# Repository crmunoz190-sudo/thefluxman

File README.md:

# thefluxman
This is the schematic and PCB to my guitar pedal, the flux man.
12K and 100Ohm resistors used instead of specific values to save on JLCPCB extended part fees.

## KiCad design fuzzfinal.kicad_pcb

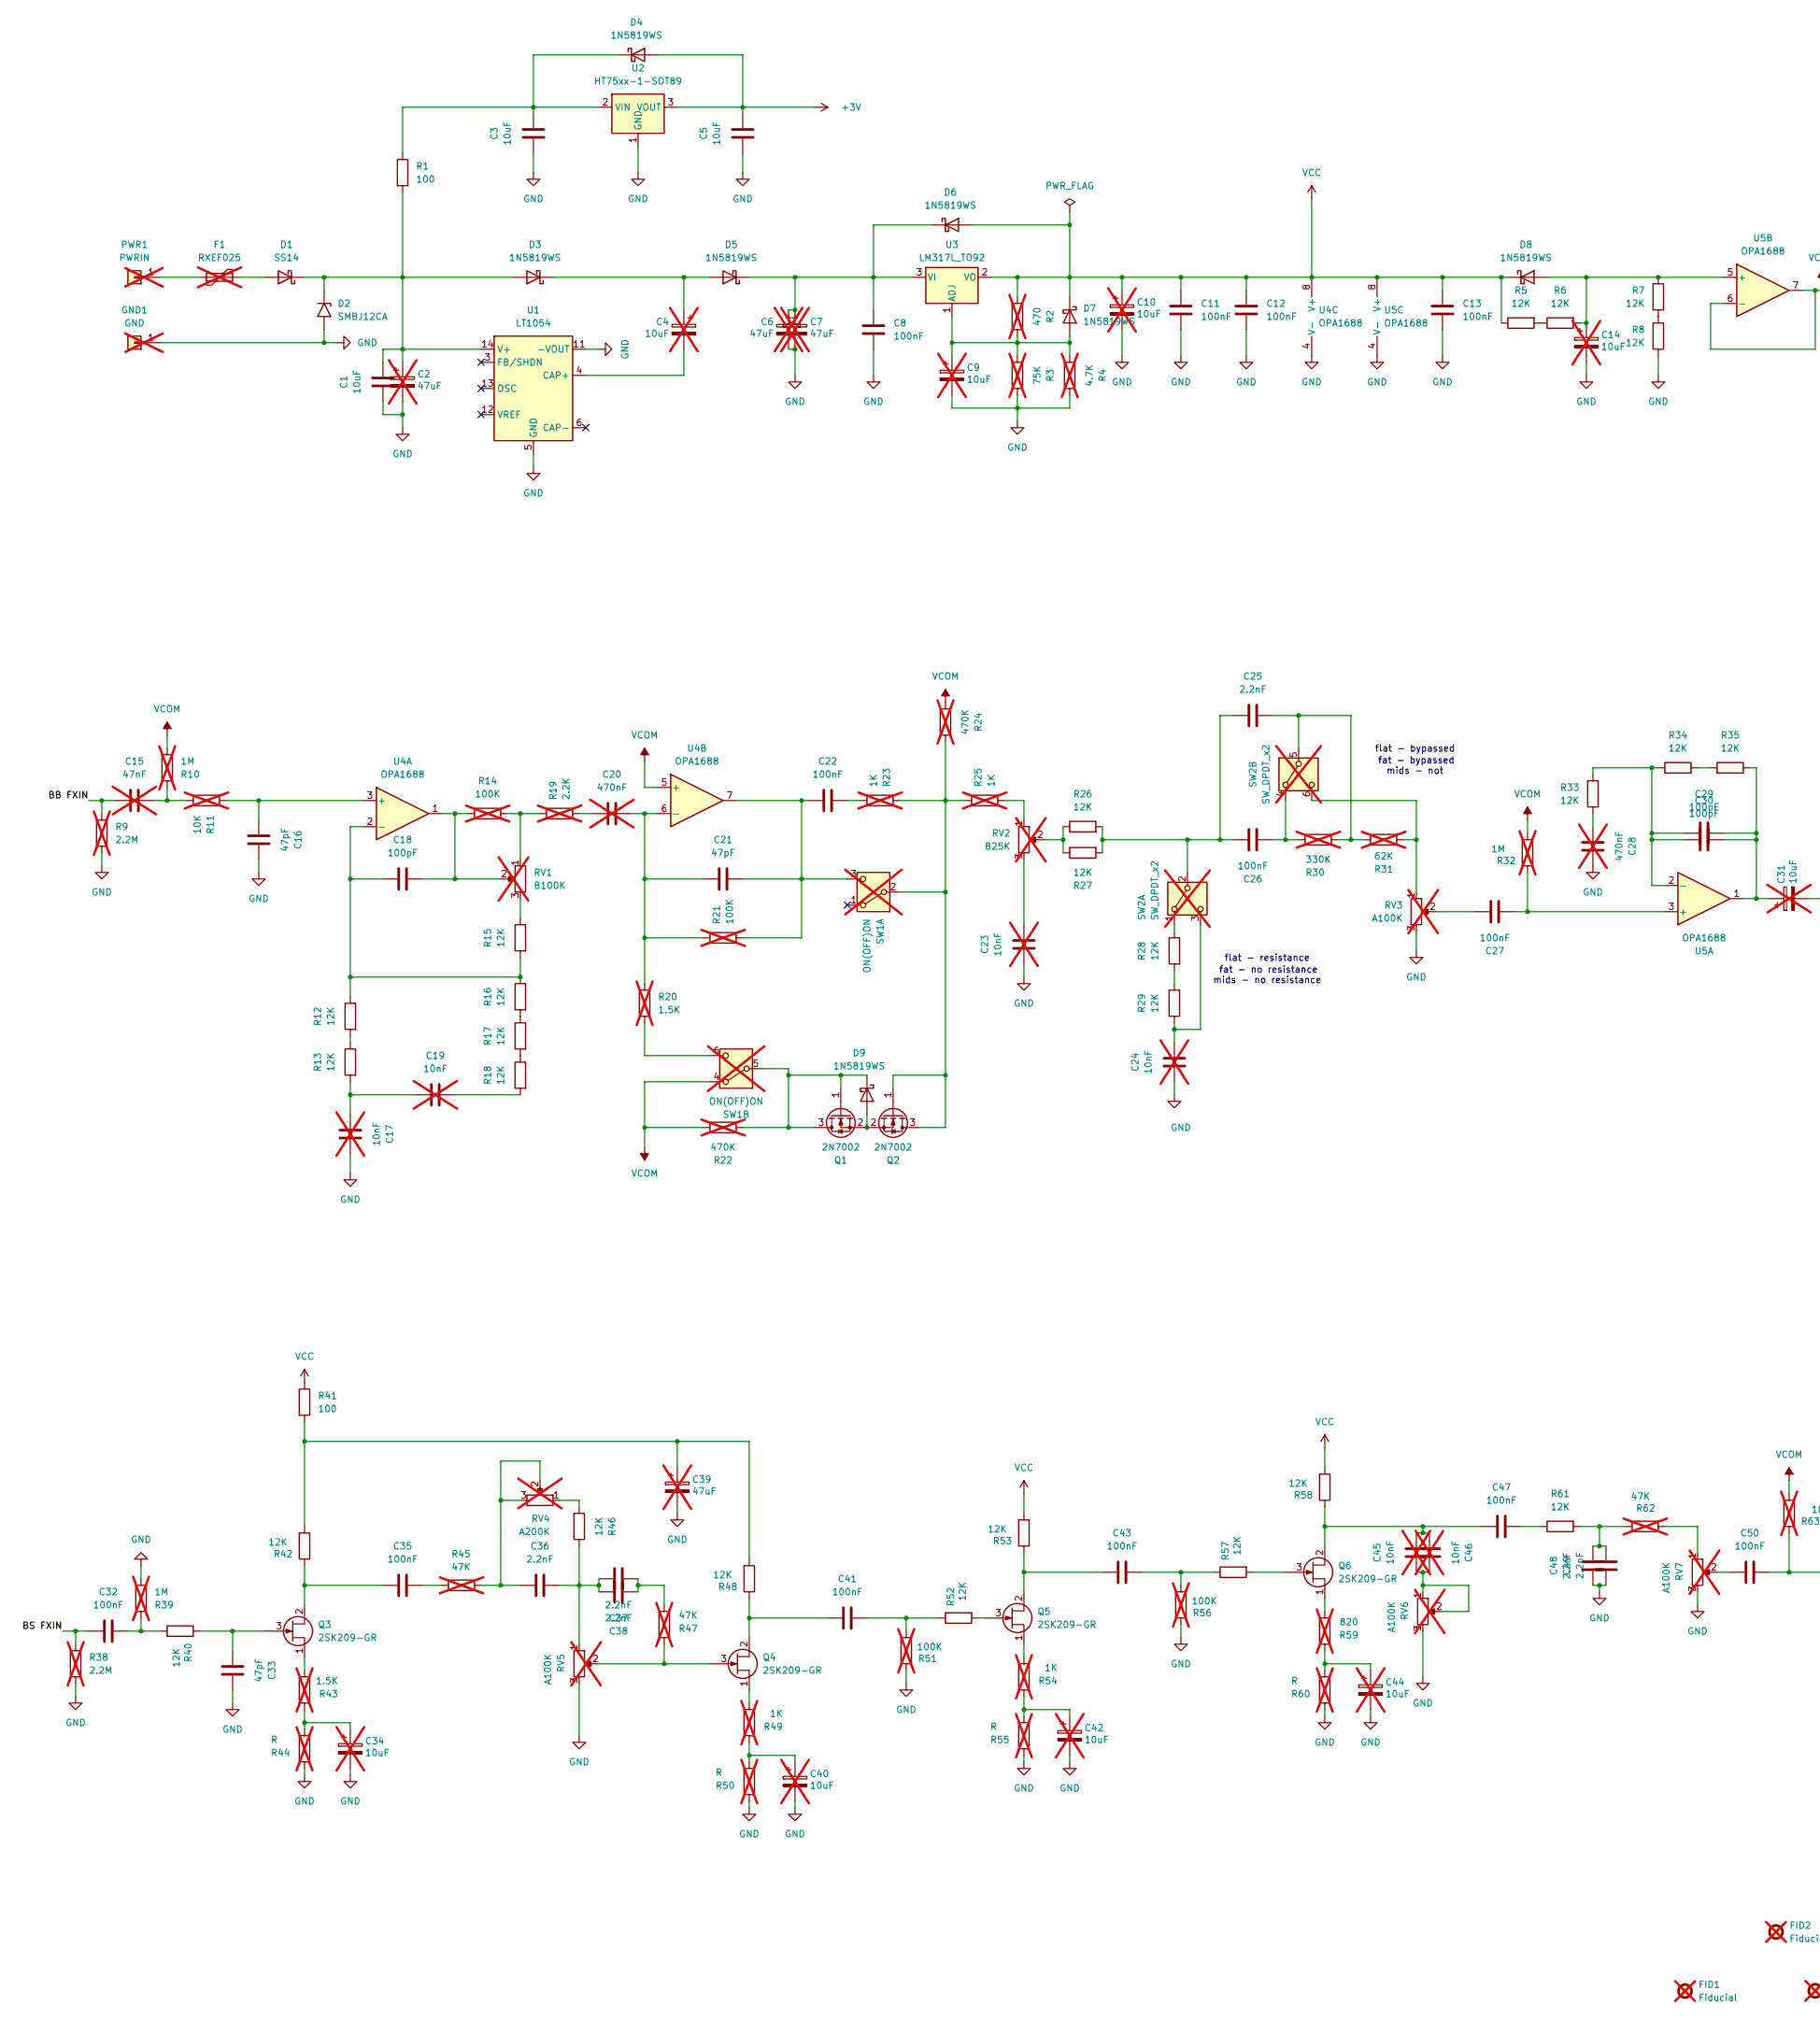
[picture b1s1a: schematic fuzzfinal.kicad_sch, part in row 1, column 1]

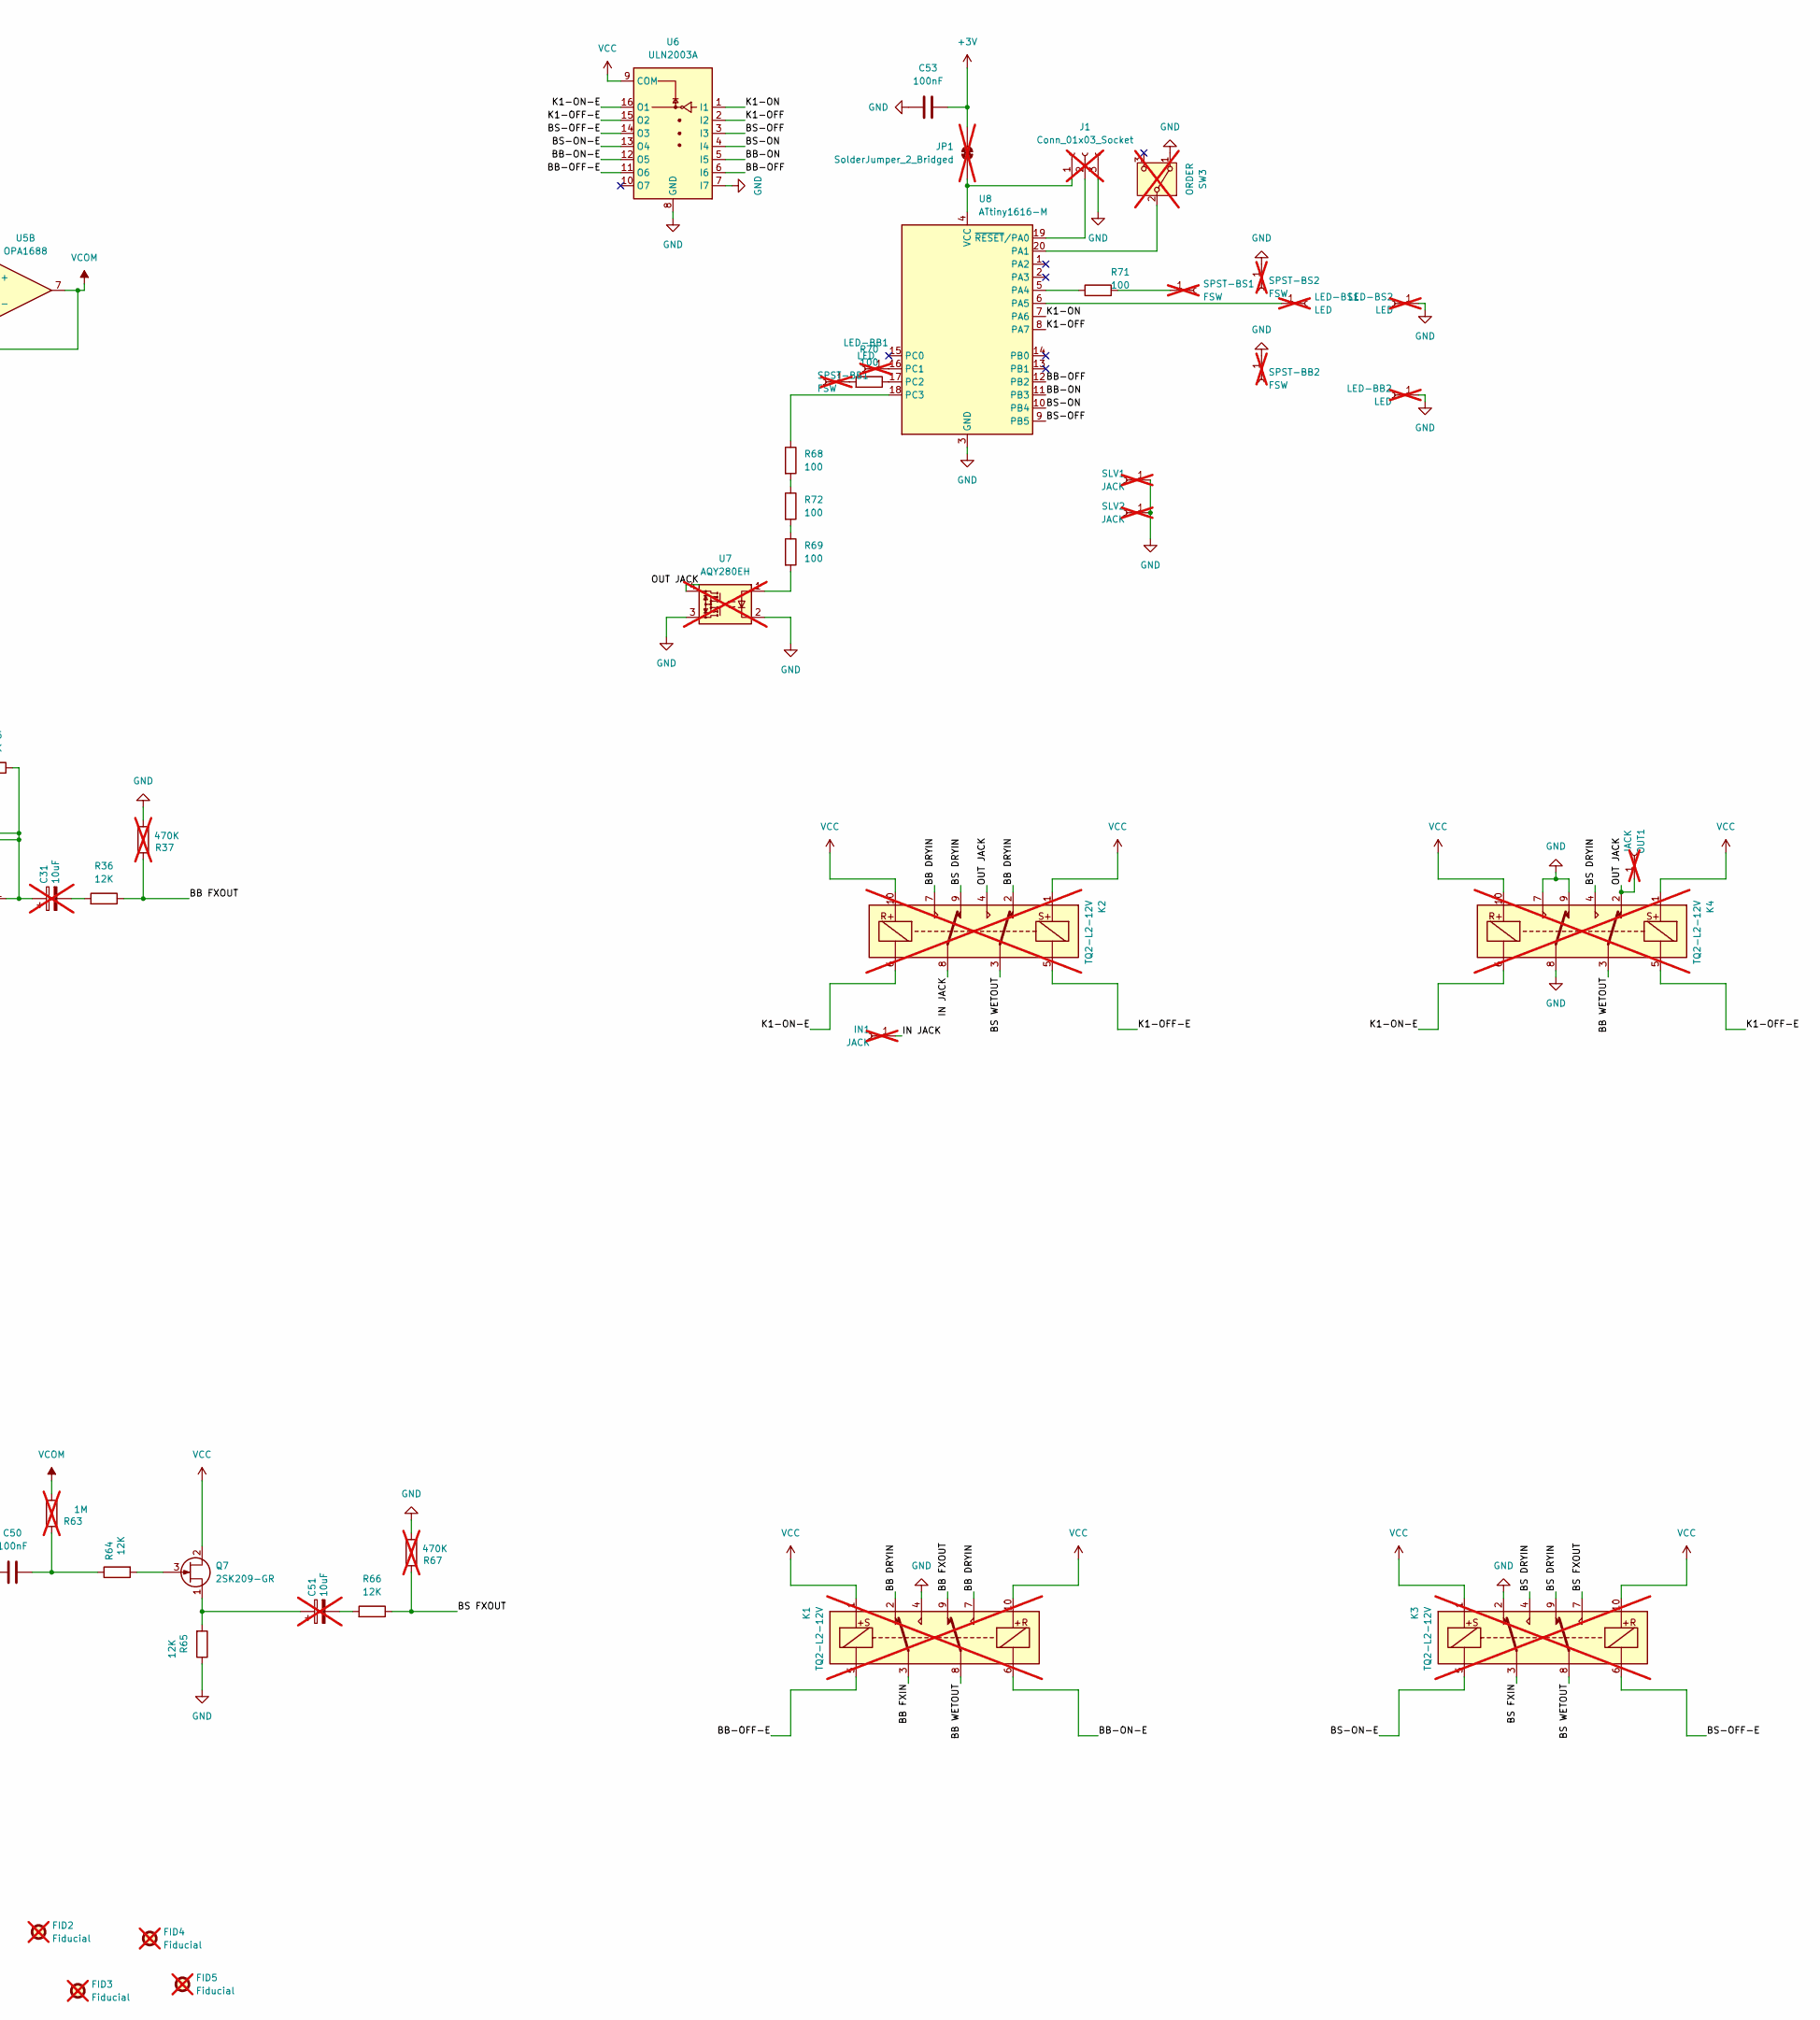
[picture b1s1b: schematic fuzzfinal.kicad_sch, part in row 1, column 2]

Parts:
C1, C3, C5: 10uF; C_0603_1608Metric; LCSC C96446
C2, C6, C7, C39: 47uF; CP_Radial_D5.0mm_P2.00mm; not fitted
C4, C9, C10, C14, C31, C34, C40, C42, C44, C51: 10uF; CP_Radial_D5.0mm_P2.00mm; not fitted
C8, C11, C12, C13, C22, C26, C27, C32, C35, C41, C43, C47, C50, C53: 100nF; C_1206_3216Metric; LCSC C363929
C15: 47nF; C_Rect_L7.2mm_W2.5mm_P5.00mm_FKS2_FKP2_MKS2_MKP2; not fitted
C16, C21, C33: 47pF; C_0402_1005Metric; LCSC C1567
C17, C19, C23, C24, C45, C46: 10nF; C_Rect_L7.2mm_W2.5mm_P5.00mm_FKS2_FKP2_MKS2_MKP2; not fitted
C18, C29, C30: 100pF; C_0402_1005Metric; LCSC C1546
C20, C28: 470nF; C_Rect_L7.2mm_W3.5mm_P5.00mm_FKS2_FKP2_MKS2_MKP2; not fitted
C25, C36, C37, C38, C48, C49: 2.2nF; C_0805_2012Metric; LCSC C28260
D1: SS14; D_SMA; LCSC C2480
D2: SMBJ12CA; D_SMB; LCSC C19077566
D3, D4, D5, D6, D7, D8, D9: 1N5819WS; D_SOD-323; LCSC C191023
F1: RXEF025; C_Rect_L7.2mm_W3.0mm_P5.00mm_FKS2_FKP2_MKS2_MKP2; not fitted
FID1, FID2, FID3, FID4, FID5: Fiducial; Fiducial_1mm_Mask2mm; not fitted
GND1: GND; Solder Wire, DC Jack NO RELIEF; not fitted
IN1: JACK; Solder Wire, DC Jack NO RELIEF; not fitted
J1: Conn_01x03_Socket; PinSocket_1x03_P2.54mm_Vertical; not fitted
JP1: SolderJumper_2_Bridged; SolderJumper-2_P1.3mm_Open_TrianglePad1.0x1.5mm; not fitted
K1, K2, K3, K4: TQ2-L2-12V; not fitted
LED-BB1, LED-BB2: LED; Solder Wire, DC Jack NO RELIEF; not fitted
LED-BS1, LED-BS2: LED; Solder Wire, DC Jack NO RELIEF; not fitted
OUT1: JACK; Solder Wire, DC Jack NO RELIEF; not fitted
PWR1: PWRIN; Solder Wire, DC Jack NO RELIEF; not fitted
Q1, Q2: 2N7002; SOT-323_SC-70; LCSC C7420322
Q3, Q4, Q5, Q6, Q7: 2SK209-GR; SC-59; LCSC C61792
R1, R41, R68, R69, R70, R71, R72: 100; R_0603_1608Metric; LCSC C22775
R2: 470; R_Axial_DIN0207_L6.3mm_D2.5mm_P7.62mm_Horizontal; not fitted
R3: 75K; R_Axial_DIN0204_L3.6mm_D1.6mm_P5.08mm_Horizontal; not fitted
R4: 4.7K; R_Axial_DIN0204_L3.6mm_D1.6mm_P7.62mm_Horizontal; not fitted
R5, R6, R7, R8, R12, R13, R15, R16, R17, R18, R26, R27, R28, R29, R33, R34, R35, R36, R40, R42, R46, R48, R52, R53, R57, R58, R61, R64, R65, R66: 12K; R_0402_1005Metric; LCSC C784579
R9, R38: 2.2M; R_Axial_DIN0204_L3.6mm_D1.6mm_P5.08mm_Horizontal; not fitted
R10, R32, R39, R63: 1M; R_Axial_DIN0204_L3.6mm_D1.6mm_P5.08mm_Horizontal; not fitted
R11: 10K; R_Axial_DIN0207_L6.3mm_D2.5mm_P7.62mm_Horizontal; not fitted
R14, R21, R51, R56: 100K; R_Axial_DIN0204_L3.6mm_D1.6mm_P5.08mm_Horizontal; not fitted
R19: 2.2K; R_Axial_DIN0207_L6.3mm_D2.5mm_P7.62mm_Horizontal; not fitted
R20: 1.5K; R_Axial_DIN0207_L6.3mm_D2.5mm_P5.08mm_Vertical; not fitted
R22, R24, R37, R67: 470K; R_Axial_DIN0204_L3.6mm_D1.6mm_P5.08mm_Horizontal; not fitted
R23, R25, R49, R54: 1K; R_Axial_DIN0207_L6.3mm_D2.5mm_P7.62mm_Horizontal; not fitted
R30: 330K; R_Axial_DIN0204_L3.6mm_D1.6mm_P5.08mm_Horizontal; not fitted
R31: 62K; R_Axial_DIN0204_L3.6mm_D1.6mm_P5.08mm_Horizontal; not fitted
R43: 1.5K; R_Axial_DIN0207_L6.3mm_D2.5mm_P7.62mm_Horizontal; not fitted
R44, R50, R55, R60: R; R_Axial_DIN0207_L6.3mm_D2.5mm_P7.62mm_Horizontal; not fitted
R45, R47, R62: 47K; R_Axial_DIN0204_L3.6mm_D1.6mm_P5.08mm_Horizontal; not fitted
R59: 820; R_Axial_DIN0207_L6.3mm_D2.5mm_P7.62mm_Horizontal; not fitted
RV1: B100K; SingleTaper16mmAlpha; not fitted
RV2: B25K; SingleTaper16mmAlpha; not fitted
RV3, RV5, RV6, RV7: A100K; SingleTaper16mmAlpha; not fitted
RV4: A200K; SingleTaper16mmAlpha; not fitted
SLV1, SLV2: JACK; Solder Wire, DC Jack NO RELIEF; not fitted
SPST-BB1, SPST-BB2: FSW; Solder Wire, DC Jack NO RELIEF; not fitted
SPST-BS1, SPST-BS2: FSW; Solder Wire, DC Jack NO RELIEF; not fitted
SW1: ON(OFF)ON; 2pdt; not fitted
SW2: SW_DPDT_x2; 2pdt; not fitted
SW3: ORDER; spdt; not fitted
U1: LT1054; SOIC-16W_7.5x10.3mm_P1.27mm; LCSC C2071368
U2: HT75xx-1-SOT89; SOT-89-3; LCSC C14289
U3: LM317L_TO92; SOT-89-3; LCSC C112537
U4, U5: OPA1688; SOIC-8_3.9x4.9mm_P1.27mm; LCSC C206212
U6: ULN2003A; SOIC-16_3.9x9.9mm_P1.27mm; LCSC C7512
U7: AQY280EH; DIP-4_W10.16mm; not fitted
U8: ATtiny1616-M; QFN-20-1EP_3x3mm_P0.4mm_EP1.65x1.65mm; LCSC C507118

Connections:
+3V: C5.1, C53.2, D4.2 (A), JP1.2 (B), U2.3 (VOUT)
/BB DRYIN: K1.2, K1.7, K2.2, K2.7
/BB FXIN: C15.1, K1.3, R9.1
/BB FXOUT: K1.9, R36.1, R37.1
/BB WETOUT: K1.8, K4.3
/BB-OFF: U6.6 (I6), U8.12 (PB2)
/BB-OFF-E: K1.5, U6.11 (O6)
/BB-ON: U6.5 (I5), U8.11 (PB3)
/BB-ON-E: K1.6, U6.12 (O5)
/BS DRYIN: K2.9, K3.4, K3.9, K4.4
/BS FXIN: C32.1, K3.3, R38.1
/BS FXOUT: K3.7, R66.1, R67.1
/BS WETOUT: K2.3, K3.8
/BS-OFF: U6.3 (I3), U8.9 (PB5)
/BS-OFF-E: K3.6, U6.14 (O3)
/BS-ON: U6.4 (I4), U8.10 (PB4)
/BS-ON-E: K3.5, U6.13 (O4)
/IN JACK: IN1.1 (Pin_1_1), K2.8
/K1-OFF: U6.2 (I2), U8.8 (PA7)
/K1-OFF-E: K2.5, K4.5, U6.15 (O2)
/K1-ON: U6.1 (I1), U8.7 (PA6)
/K1-ON-E: K2.6, K4.6, U6.16 (O1)
/OUT JACK: K2.4, K4.2, OUT1.1 (Pin_1_1), U7.4
GND: C1.2, C2.2, C3.2, C5.2, C6.2, C7.2, C8.1, C9.2, C10.2, C11.1, C12.1, C13.1, C14.2, C16.1, C17.1, C23.2, C24.2, C28.2, C33.1, C34.2, C39.2, C40.2, C42.2, C44.2, C48.2, C49.2, C53.1, D2.2 (A2), GND1.1 (Pin_1_1), J1.3, K1.4, K3.2, K4.7, K4.8, K4.9, LED-BB2.1 (Pin_1_1), LED-BS2.1 (Pin_1_1), R3.1, R4.1, R8.1, R9.2, R37.2, R38.2, R39.2, R44.1, R50.1, R51.1, R55.1, R56.1, R60.1, R65.1, R67.2, RV3.3, RV5.3, RV6.3, RV7.3, SLV1.1 (Pin_1_1), SLV2.1 (Pin_1_1), SPST-BB2.1 (Pin_1_1), SPST-BS2.1 (Pin_1_1), SW3.1 (A), U1.5 (GND), U1.11 (-VOUT), U2.1 (GND), U4.4 (V-), U5.4 (V-), U6.7 (I7), U6.8 (GND), U7.2, U7.3, U8.3 (GND), U8.21 (GND)
unnamed: C15.2, R10.1, R11.2
unnamed: C17.2, C19.2, R13.2
unnamed: C18.1, R14.2, RV1.2, U4.1
unnamed: C19.1, R18.2
unnamed: C20.1, R19.2
unnamed: C22.1, R23.2
unnamed: C23.1, RV2.3
unnamed: C27.1, RV3.2
unnamed: C28.1, R33.1
unnamed: C29.1, C30.2, C31.1, R35.1, U5.1
unnamed: C31.2, R36.2
unnamed: C32.2, R39.1, R40.2
unnamed: C34.1, R43.1, R44.2
unnamed: C35.2, R45.2
unnamed: C36.1, R45.1, RV4.2, RV4.3
unnamed: C36.2, C37.1, C38.1, R46.1, RV5.1
unnamed: C37.2, C38.2, R47.2
unnamed: C39.1, R41.2, R42.2, R48.2
unnamed: C40.1, R49.1, R50.2
unnamed: C41.2, R51.2, R52.1
unnamed: C42.1, R54.1, R55.2
unnamed: C43.2, R56.2, R57.1
unnamed: C44.1, R59.1, R60.2
unnamed: C45.2, C46.2, RV6.1, RV6.2
unnamed: C47.1, R61.1
unnamed: C48.1, C49.1, R61.2, R62.1
unnamed: C50.1, R63.1, R64.1
unnamed: C50.2, RV7.2
unnamed: C51.2, R66.2
unnamed: D1.2 (A), F1.2
unnamed: C1.1, C2.1, D1.1 (K), D2.1 (A1), D3.2 (A), R1.2, U1.14 (V+)
unnamed: C4.1, D3.1 (K), D5.2 (A)
unnamed: C3.1, D4.1 (K), R1.1, U2.2 (VIN)
unnamed: C6.1, C7.1, C8.2, D5.1 (K), D6.1 (K), U3.3 (VI)
unnamed: C9.1, D7.2 (A), R2.1, R3.2, R4.2, U3.1 (ADJ)
unnamed: C14.1, D8.2 (A), R6.2, R7.2, U5.5 (+)
unnamed: D9.2 (A), Q1.2 (S), Q2.2 (S)
unnamed: D9.1 (K), Q1.1 (G), Q1.3 (D), R22.1, SW1.5 (B)
unnamed: J1.1, JP1.1 (A), U8.4 (VCC)
unnamed: J1.2, U8.19 (~RESET/PA0)
unnamed: LED-BB1.1 (Pin_1_1), U8.16 (PC1)
unnamed: LED-BS1.1 (Pin_1_1), U8.6 (PA5)
unnamed: F1.1, PWR1.1 (Pin_1_1)
unnamed: Q2.1 (G), Q2.3 (D), R23.1, R24.2, R25.1, SW1.2 (B)
unnamed: C35.1, Q3.2 (D), R42.1
unnamed: C33.2, Q3.3 (G), R40.1
unnamed: Q3.1 (S), R43.2
unnamed: C41.1, Q4.2 (D), R48.1
unnamed: Q4.3 (G), R47.1, RV5.2
unnamed: Q4.1 (S), R49.2
unnamed: C43.1, Q5.2 (D), R53.1
unnamed: Q5.3 (G), R52.2
unnamed: Q5.1 (S), R54.2
unnamed: C45.1, C46.1, C47.2, Q6.2 (D), R58.1
unnamed: Q6.3 (G), R57.2
unnamed: Q6.1 (S), R59.2
unnamed: Q7.3 (G), R64.2
unnamed: C51.1, Q7.1 (S), R65.2
unnamed: R5.2, R6.1
unnamed: R7.1, R8.2
unnamed: R12.2, R13.1
unnamed: R14.1, R19.1, RV1.1
unnamed: R15.1, RV1.3
unnamed: R16.2, R17.1
unnamed: R17.2, R18.1
unnamed: R25.2, RV2.1
unnamed: R26.1, R27.1, RV2.2
unnamed: R28.2, R29.2
unnamed: R34.2, R35.2
unnamed: R46.2, RV4.1
unnamed: R62.2, RV7.1
unnamed: R68.2, R72.1
unnamed: R69.1, R72.2
unnamed: R69.2, U7.1
unnamed: R70.2, SPST-BB1.1 (Pin_1_1)
unnamed: R71.2, SPST-BS1.1 (Pin_1_1)
unnamed: C21.1, C22.2, R21.2, SW1.3 (C), U4.7
unnamed: R20.2, SW1.6 (C)
unnamed: R28.1, SW2.1 (A)
unnamed: C25.1, C26.1, R26.2, R27.2, SW2.2 (B)
unnamed: C24.1, R29.1, SW2.3 (C)
unnamed: C26.2, R30.1, SW2.4 (A)
unnamed: C25.2, R30.2, R31.1, SW2.5 (B)
unnamed: R31.2, RV3.1, SW2.6 (C)
unnamed: SW3.2 (B), U8.20 (PA1)
unnamed: C4.2, U1.4 (CAP+)
unnamed: C16.2, R11.1, U4.3 (+)
unnamed: C18.2, R12.1, R15.2, R16.1, U4.2 (-)
unnamed: C20.2, C21.2, R20.1, R21.1, U4.6 (-)
unnamed: C27.2, R32.1, U5.3 (+)
unnamed: C29.2, C30.1, R33.2, R34.1, U5.2 (-)
unnamed: R71.1, U8.5 (PA4)
unnamed: R70.1, U8.17 (PC2)
unnamed: R68.1, U8.18 (PC3)
VCC: C10.1, C11.2, C12.2, C13.2, D6.2 (A), D7.1 (K), D8.1 (K), K1.1, K1.10, K2.1, K2.10, K3.1, K3.10, K4.1, K4.10, Q7.2 (D), R2.2, R5.1, R41.1, R53.2, R58.2, U3.2 (VO), U4.8 (V+), U5.8 (V+), U6.9 (COM)
VCOM: R10.2, R22.2, R24.1, R32.2, R63.2, SW1.4 (A), U4.5 (+), U5.6 (-), U5.7

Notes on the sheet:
mids - not
mids - no resistance
flat - resistance
fat - no resistance
flat - bypassed
fat - bypassed

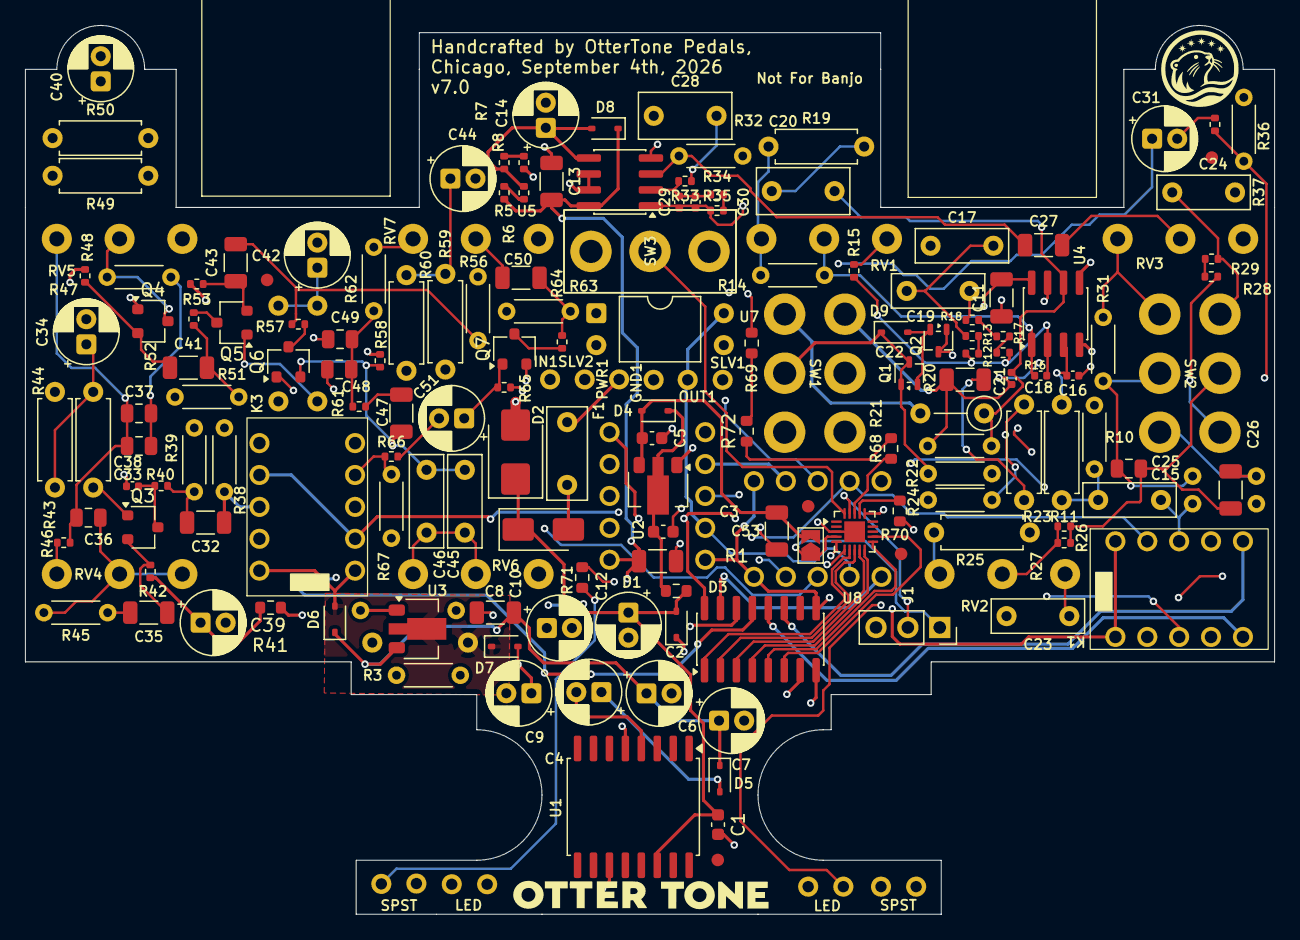
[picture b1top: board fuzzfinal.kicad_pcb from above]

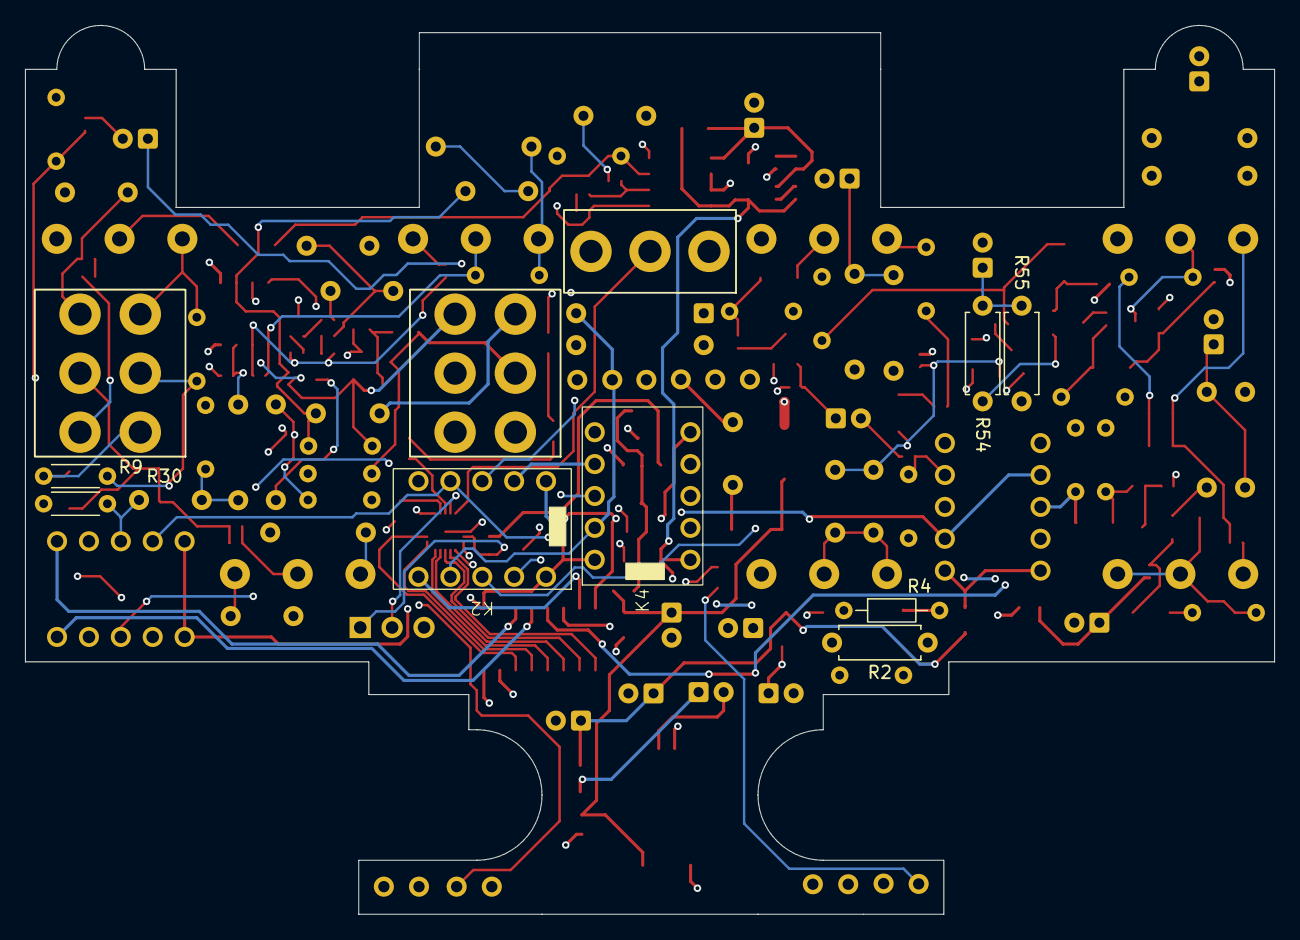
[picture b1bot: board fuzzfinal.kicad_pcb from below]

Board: 4 copper layers, 99.5 x 70.8 mm, 184 parts (8 on the bottom side), 120 nets.
